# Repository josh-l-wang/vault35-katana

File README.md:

# vault35-katana
 katana stagger for vault35 by mechvault

## Firmware:
Firmware source is available in vial-qmk main branch. The precompiled .bin is in the firmware folder in this repository. To put the board into bootloader, hold down the reset button while plugging it in or use bootmagic. Flash using QMK Toolbox.

## PCB
### PCB Renders

### Layout Options

Note: The encoder spots share one set of pins, so you will not get two unique inputs if you solder encoders into both spots.

## Plate
Two plate options exist. Both support all 7 bottom row options. The 1u plate has blockers on the top right and left corners to support 1u keys in those corners. The universal plate supports the top corners that support 1.5u and 1.25 corner keys and/or ISO enter to make a rectangular key layout (as well as 1u keys in the corners, though the PCB will be visible through the switch cutouts of the plate).

### 1u

### Uiversal

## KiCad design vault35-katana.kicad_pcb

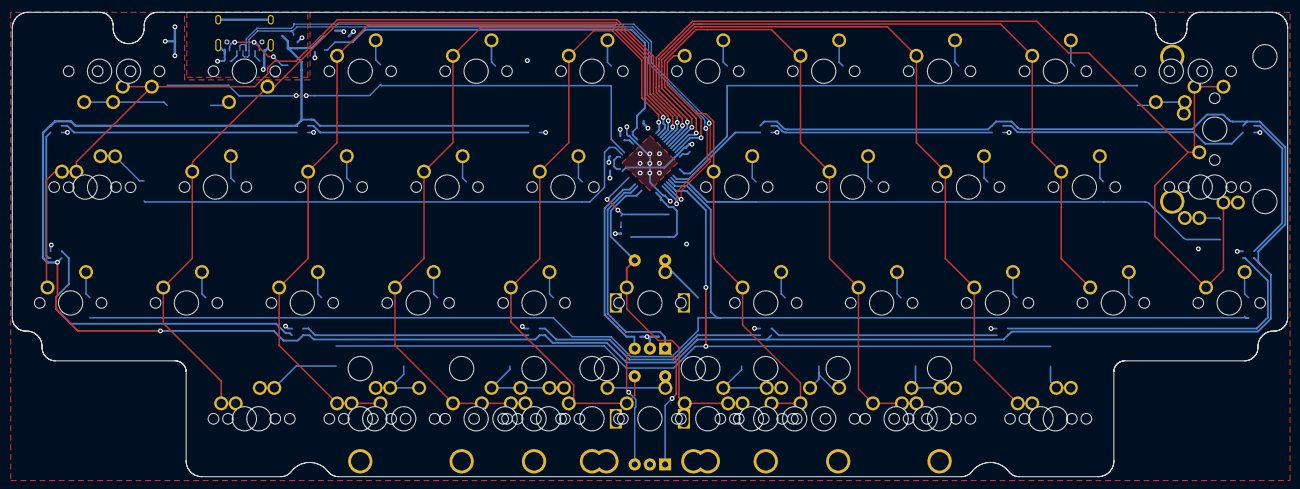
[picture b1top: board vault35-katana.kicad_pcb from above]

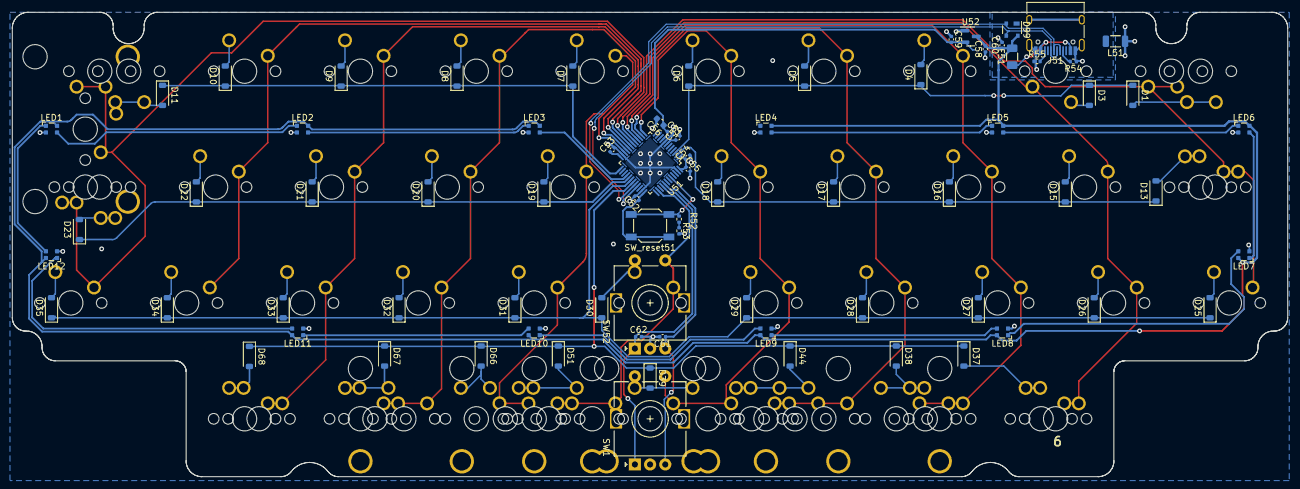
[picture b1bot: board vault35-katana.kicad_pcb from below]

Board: 2 copper layers, 209.7 x 76.3 mm, 139 parts (76 on the bottom side), 81 nets.

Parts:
C51, C52, C53, C54, C55, C57, C60, C61, C62: 100nF; C_0402_1005Metric
C56: 10uF; C_0603_1608Metric
C58, C59: 1uF; C_0402_1005Metric
D1, D3, D4, D5, D6, D7, D8, D9, D10, D11, D13, D15, D16, D17, D18, D19, D20, D21, D22, D23, D25, D26, D27, D28, D29, D30, D31, D32, D33, D34, D35, D37, D38, D39, D44, D51, D66, D67, D68: D_Small; D_SOD-123
D99: PRTR5V0U2X; SOT-143
F51: ASMD1206-150; Fuse_1206_3216Metric
J51: USB_C_Receptacle_USB2.0; USB_C_Receptacle_HRO_TYPE-C-31-M-12
L51: 60R@100MHz; L_1206_3216Metric
LED1, LED2, LED3, LED4, LED5, LED6, LED7, LED8, LED9, LED10, LED11, LED12: WS2812-2020; LED_WS2812_2020
MX1, MX3, MX4, MX5, MX6, MX7, MX8, MX9, MX10, MX12, MX13, MX15, MX16, MX17, MX18, MX19, MX20, MX21, MX22, MX24, MX25, MX26, MX27, MX28, MX29, MX30, MX31, MX32, MX33, MX34, MX35, MX36, MX39, MX50, MX51, MX61, MX62, MX63, MX64, MX65, MX66, MX67, MX68: MX_SW_solder; SW_MX_1u
MX2, MX11, MX42, MX47: MX_SW_solder; SW_MX_1.5u
MX14, MX23, MX37, MX38, MX40, MX41, MX43, MX46: MX_SW_solder; SW_MX_1.25u
MX44, MX45: MX_SW_solder; SW_MX_1.75u
R52, R53, R54, R55: 5.1k; R_0402_1005Metric
S1: MX_stab; STAB_MX_P_ISO
S2, S5, S6: MX_stab; STAB_MX_P_3u
S3, S4: MX_stab; STAB_MX_P_2u
SW1, SW52: Rotary_Encoder_Switch; RotaryEncoder_Alps_EC11E-Switch_Vertical_H20mm
SW_reset51: SKQGABE010; SW_SPST_SKQG_WithoutStem
U51: STM32F072CBT6; LQFP-48_7x7mm_P0.5mm
U52: XC6206P332MR-Regulator_Linear; SOT-23

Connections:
+3V3: C51.1, C52.1, C53.1, C54.1, C55.1, C56.1, C59.2, SW_reset51.1, U51.1 (VBAT), U51.9 (VDDA), U51.24 (VDD), U51.36 (VDDIO2), U51.48 (VDD), U52.2 (VO)
+5V: C58.2, C60.1, D99.4 (VCC), F51.2, LED1.4 (VDD), LED2.4 (VDD), LED3.4 (VDD), LED4.4 (VDD), LED5.4 (VDD), LED6.4 (VDD), LED7.4 (VDD), LED8.4 (VDD), LED9.4 (VDD), LED10.4 (VDD), LED11.4 (VDD), LED12.4 (VDD), U52.3 (VI)
BOOT0: R52.1, SW_reset51.2, U51.44 (BOOT0)
D_N: D99.2 (I/O1), J51.A7 (D-), J51.B7 (D-), U51.32 (PA11)
D_P: D99.3 (I/O2), J51.A6 (D+), J51.B6 (D+), U51.33 (PA12)
EncA: C62.1, SW1.A, SW52.A, U51.40 (PB4)
EncB: C61.1, SW1.B, SW52.B, U51.41 (PB5)
GND: C51.2, C52.2, C53.2, C54.2, C55.2, C56.2, C57.2, C58.1, C59.1, C60.2, C61.2, C62.2, J51.A1 (GND), J51.A12 (GND), J51.B1 (GND), J51.B12 (GND), J51.S1 (SHIELD), L51.1, L51.2, LED1.2 (VSS), LED2.2 (VSS), LED3.2 (VSS), LED4.2 (VSS), LED5.2 (VSS), LED6.2 (VSS), LED7.2 (VSS), LED8.2 (VSS), LED9.2 (VSS), LED10.2 (VSS), LED11.2 (VSS), LED12.2 (VSS), R53.2, R54.1, R55.1, SW1.C, SW52.C, U51.8 (VSSA), U51.23 (VSS), U51.35 (VSS), U51.47 (VSS), U52.1 (GND)
NRST: C57.1, U51.7 (NRST)
unnamed: D1.2 (A), MX1.2, MX2.2
unnamed: D3.2 (A), MX3.2
unnamed: D4.2 (A), MX4.2
unnamed: D5.2 (A), MX5.2
unnamed: D6.2 (A), MX6.2
unnamed: D7.2 (A), MX7.2
unnamed: D8.2 (A), MX8.2
unnamed: D9.2 (A), MX9.2
unnamed: D10.2 (A), MX10.2
unnamed: D11.2 (A), MX11.2, MX12.2, MX36.2
unnamed: D13.2 (A), MX13.2, MX14.2
unnamed: D15.2 (A), MX15.2
unnamed: D16.2 (A), MX16.2
unnamed: D17.2 (A), MX17.2
unnamed: D18.2 (A), MX18.2
unnamed: D19.2 (A), MX19.2
unnamed: D20.2 (A), MX20.2
unnamed: D21.2 (A), MX21.2
unnamed: D22.2 (A), MX22.2
unnamed: D23.2 (A), MX23.2, MX24.2
unnamed: D25.2 (A), MX25.2
unnamed: D26.2 (A), MX26.2
unnamed: D27.2 (A), MX27.2
unnamed: D28.2 (A), MX28.2
unnamed: D29.2 (A), MX29.2
unnamed: D30.2 (A), MX30.2, SW52.S2
unnamed: D31.2 (A), MX31.2
unnamed: D32.2 (A), MX32.2
unnamed: D33.2 (A), MX33.2
unnamed: D34.2 (A), MX34.2
unnamed: D35.2 (A), MX35.2
unnamed: D37.2 (A), MX37.2, MX61.2
unnamed: D38.2 (A), MX38.2, MX43.2, MX62.2
unnamed: D39.2 (A), MX39.2, MX64.2, SW1.S2
unnamed: D44.2 (A), MX42.2, MX44.2, MX50.2, MX63.2
unnamed: D51.2 (A), MX45.2, MX51.2, MX65.2
unnamed: D66.2 (A), MX47.2, MX66.2
unnamed: D67.2 (A), MX40.2, MX46.2, MX67.2
unnamed: D68.2 (A), MX41.2, MX68.2
unnamed: J51.A5 (CC1), R54.2
unnamed: J51.B5 (CC2), R55.2
unnamed: LED1.3 (DIN), LED2.1 (DOUT)
unnamed: LED1.1 (DOUT), LED12.3 (DIN)
unnamed: LED2.3 (DIN), LED3.1 (DOUT)
unnamed: LED4.3 (DIN), LED5.1 (DOUT)
unnamed: LED5.3 (DIN), LED6.1 (DOUT)
unnamed: LED6.3 (DIN), LED7.1 (DOUT)
unnamed: LED7.3 (DIN), LED8.1 (DOUT)
unnamed: LED8.3 (DIN), LED9.1 (DOUT)
unnamed: LED10.3 (DIN), LED11.1 (DOUT)
unnamed: LED9.3 (DIN), LED10.1 (DOUT)
unnamed: LED11.3 (DIN), LED12.1 (DOUT)
unnamed: R52.2, R53.1
RGB: LED3.3 (DIN), U51.28 (PB15)
VBUS: F51.1, J51.A4 (VBUS), J51.A9 (VBUS), J51.B4 (VBUS), J51.B9 (VBUS)
col0: MX1.1, MX2.1, MX13.1, MX14.1, MX25.1, U51.17 (PA7)
col1: MX3.1, MX15.1, MX26.1, MX37.1, MX61.1, U51.16 (PA6)
col2: MX4.1, MX16.1, MX27.1, MX38.1, MX43.1, MX62.1, U51.15 (PA5)
col3: MX5.1, MX17.1, MX28.1, MX42.1, MX44.1, MX50.1, MX63.1, U51.14 (PA4)
col4: MX6.1, MX18.1, MX29.1, MX39.1, MX64.1, SW1.S1, U51.13 (PA3)
col5: MX30.1, MX45.1, MX51.1, MX65.1, SW52.S1, U51.38 (PA15)
col6: MX7.1, MX19.1, MX31.1, MX47.1, MX66.1, U51.22 (PB11)
col7: MX8.1, MX20.1, MX32.1, MX40.1, MX46.1, MX67.1, U51.21 (PB10)
col8: MX9.1, MX21.1, MX33.1, MX41.1, MX68.1, U51.20 (PB2)
col9: MX10.1, MX22.1, MX34.1, U51.19 (PB1)
col10: MX11.1, MX12.1, MX23.1, MX24.1, MX35.1, MX36.1, U51.18 (PB0)
row0: D1.1 (K), D3.1 (K), D4.1 (K), D5.1 (K), D6.1 (K), U51.3 (PC14)
row1: D7.1 (K), D8.1 (K), D9.1 (K), D10.1 (K), D11.1 (K), U51.25 (PB12)
row2: D13.1 (K), D15.1 (K), D16.1 (K), D17.1 (K), D18.1 (K), U51.2 (PC13)
row3: D19.1 (K), D20.1 (K), D21.1 (K), D22.1 (K), D23.1 (K), U51.29 (PA8)
row4: D25.1 (K), D26.1 (K), D27.1 (K), D28.1 (K), D29.1 (K), D30.1 (K), D31.1 (K), D32.1 (K), D33.1 (K), D34.1 (K), D35.1 (K), U51.30 (PA9)
row5: D37.1 (K), D38.1 (K), D39.1 (K), D44.1 (K), D51.1 (K), D66.1 (K), D67.1 (K), D68.1 (K), U51.31 (PA10)

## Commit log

2023-10-28 v0.1 pcb files uploaded
2023-10-29 Update LICENSE
    license updated to MIT
2023-10-29 updated plate images
2023-10-29 updated images again
2023-11-06 added firmware
2023-11-06 update firmware
2023-11-06 compiled firmware
2023-11-07 update firmware for more RGB brightness
2023-11-21 elecrow production files
2024-01-09 update plates
2024-01-09 clean up footprints and firmware
2024-03-12 ciantha plate
